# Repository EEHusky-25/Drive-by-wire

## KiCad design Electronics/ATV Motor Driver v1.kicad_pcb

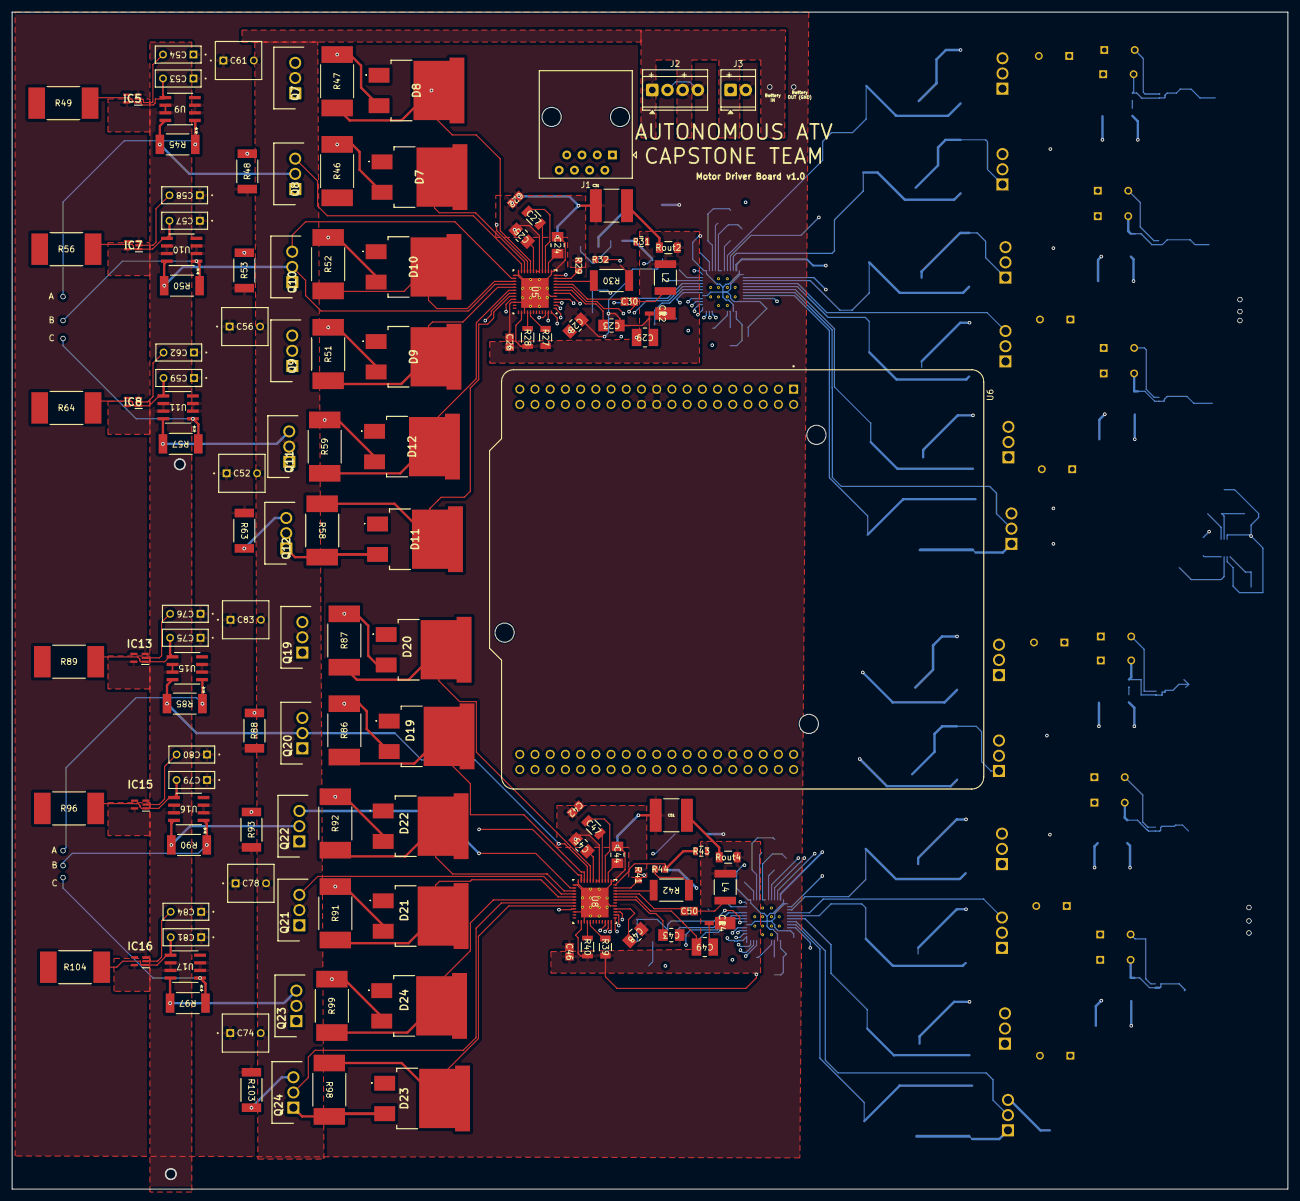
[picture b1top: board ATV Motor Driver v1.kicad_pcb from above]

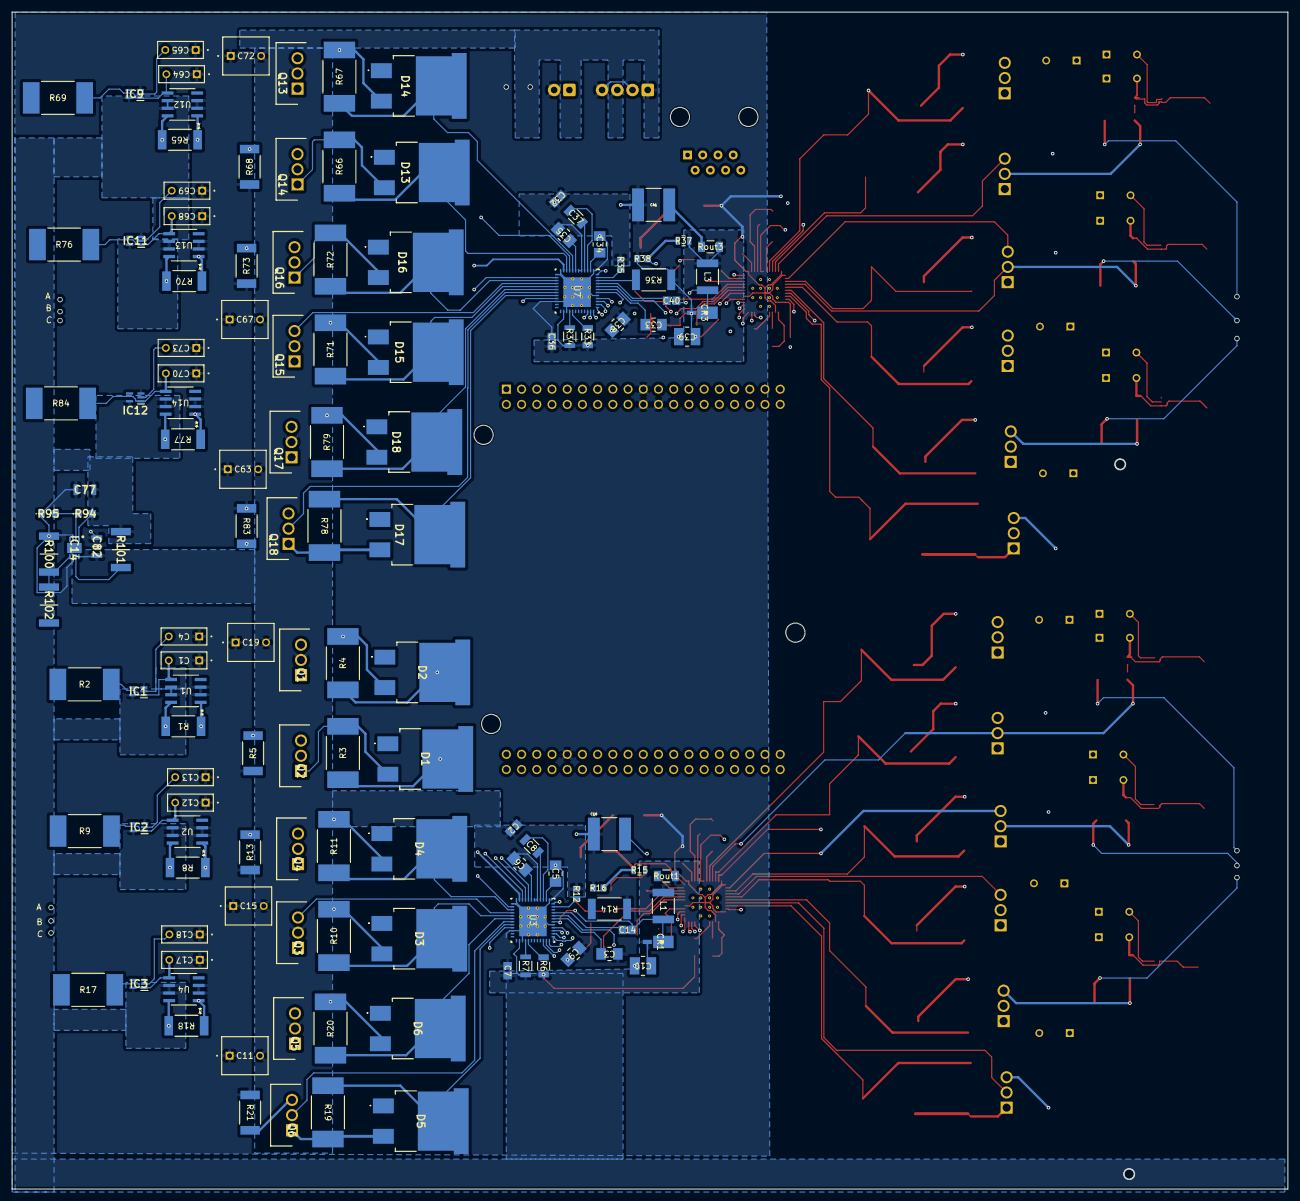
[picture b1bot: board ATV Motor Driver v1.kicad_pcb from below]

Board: 4 copper layers, 213.0 x 196.5 mm, 260 parts (132 on the bottom side), 210 nets.

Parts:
C1, C12, C17, C53, C57, C59, C64, C68, C70, C75, C79, C81: R82EC1100AA50J; CAP_R82E-7P4X2P6-5P0_KEM
C2, C7, C22, C26, C32, C36, C42, C46: C0805C104K1RECAUTO; CAPC220145_110N_KEM
C3, C5, C6, C9, C23, C24, C25, C28, C33, C34, C35, C38, C43, C44, C45, C48: C1206X105K1RACAUTO; CAPC370195_180N_KEM
C4, C13, C18, C54, C58, C62, C65, C69, C73, C76, C80, C84: R82EC2150AA50K; CAP_R82E-7P4X2P6-5P0_KEM
C8, C27, C37, C47: C1206C474K1RECAUTO; CAPC340180_180N_KEM
C10, C29, C39, C49: C1210X474K1RACAUTO; CAPC370290_115N_KEM
C11, C15, C19, C52, C56, C61, C63, C67, C72, C74, C78, C83: R82EC4100DQ70J; CAP_R82E-7P5X6P1-5P0_KEM
C14, C30, C40, C50: C0805C103K1RACAUTO; CAPC220145_88N_KEM
C16, C31, C41, C51: KRM55WR72A226MH01L; CAPC6153X670N
C77, C82: CGA5L2X7R1E105K160AA; CAPC3216X190N
CR1, CR2, CR3, CR4: UPS115UE3/TR7; POWERMITE1_DO-216AA_MIS_MCH
D1, D2, D3, D4, D5, D6, D7, D8, D9, D10, D11, D12, D13, D14, D15, D16, D17, D18, D19, D20, D21, D22, D23, D24: YQ20NL10SDTL; YQ30NL10SEFHTL
IC1, IC2, IC3, IC5, IC7, IC8, IC9, IC11, IC12, IC13, IC15, IC16: SN74LVC1G66DCKR; SOT65P210X110-5N
IC14: ADPL42005ACPZ-5.0-R7; SON50P300X300X85-9N-D
J1: RJ45; RJ45_Amphenol_54602-x08_Horizontal
J2: Screw_Terminal_01x04; TerminalBlock_TE_282834-4_1x04_P2.54mm_Horizontal
J3: Screw_Terminal_01x02; TerminalBlock_TE_282834-2_1x02_P2.54mm_Horizontal
L1, L2, L3, L4: B82432T1274K000; IND_EPCOS_B82432T_EPC
Q1, Q2, Q3, Q4, Q5, Q6, Q7, Q8, Q9, Q10, Q11, Q12, Q13, Q14, Q15, Q16, Q17, Q18, Q19, Q20, Q21, Q22, Q23, Q24: R6020ENXC7G; TO254P500X1010X2050-3P
R1, R5, R8, R13, R18, R21, R45, R48, R50, R53, R57, R63, R65, R68, R70, R73, R77, R83, R85, R88, R90, R93, R97, R103: VMS-R500-1.0-U; RES_VMS-R500-1.0-U_IAT
R2, R3, R4, R9, R10, R11, R17, R19, R20, R46, R47, R49, R51, R52, R56, R58, R59, R64, R66, R67, R69, R71, R72, R76, R78, R79, R84, R86, R87, R89, R91, R92, R96, R98, R99, R104: 35501K0JT; RES_3550_TEC
R6, R27, R33, R39: RMCF1206JT1K00; STA_RMCF1206_STP
R7, R28, R34, R40: RNCF1206TKY10K0; STA_RNCF1206_STP
R12, R29, R35, R41: ERJ-6ENF3243V; RC0805N_PAN
R14, R30, R36, R42: RMCF2512FT332K; RES_RMCF2512_STP
R15, R31, R37, R43: CRCW08053K01FKEA; RES_CRCW_0805
R16, R32, R38, R44: ERA-6AEB102V; RC0805N_PAN
R94: ERJ-UP6D6202V; ERJUP6
R95: ERJ-UP6D2002V; ERJUP6
R100, R101, R102: RCV2512100KFKEGAT; RESC6332X70N
Rout1, Rout2, Rout3, Rout4: RMCF1206FT3R00; RES_RMCF1206_STP
U1, U2, U4, U9, U10, U11, U12, U13, U14, U15, U16, U17: AD8418WBRZ; R_8_ADI
U3, U5, U7, U8: DRV8353RHRGZR; RGZ0048L
U6: NUCLEO-L476RG; MODULE_NUCLEO-L476RG

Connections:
/3-Phase H-Bridge1/CURRENT_FILTER: IC5.4 (C), IC7.4 (C), IC8.4 (C)
/3-Phase H-Bridge1/GH_A1: D8.2 (K_1), R47.1, U5.8 (GHA)
/3-Phase H-Bridge1/GH_B1: D9.2 (K_1), R51.1, U5.17 (GHB)
/3-Phase H-Bridge1/GH_C1: D12.2 (K_1), R59.1, U5.18 (GHC)
/3-Phase H-Bridge1/GL_A1: D7.2 (K_1), R46.1, U5.10 (GLA)
/3-Phase H-Bridge1/GL_B1: D10.2 (K_1), R52.1, U5.15 (GLB)
/3-Phase H-Bridge1/GL_C1: D11.2 (K_1), R58.1, U5.20 (GLC)
/3-Phase H-Bridge1/PH_A: R45.1, U9.1 (-IN)
/3-Phase H-Bridge1/PH_B: R50.1, U10.1 (-IN)
/3-Phase H-Bridge1/PH_C: R57.1, U11.1 (-IN)
/3-Phase H-Bridge1/SH_A1: Q7.3 (S), Q8.2 (D), R45.2, U5.9 (SHA), U9.8 (+IN)
/3-Phase H-Bridge1/SH_B1: Q9.3 (S), Q10.2 (D), R50.2, U5.16 (SHB), U10.8 (+IN)
/3-Phase H-Bridge1/SH_C1: Q11.3 (S), Q12.2 (D), R57.2, U5.19 (SHC), U11.8 (+IN)
/3-Phase H-Bridge1/SPA1: Q8.3 (S), R48.2, U5.11 (SPA)
/3-Phase H-Bridge1/SPB1: Q10.3 (S), R53.2, U5.14 (SPB)
/3-Phase H-Bridge1/SPC1: Q12.3 (S), R63.2, U5.21 (SPC)
/3-Phase H-Bridge1/SW1: C53.2, IC5.1 (A), R49.2, U9.5 (OUT)
/3-Phase H-Bridge1/SW2: C57.2, IC7.1 (A), R56.2, U10.5 (OUT)
/3-Phase H-Bridge1/SW3: C59.2, IC8.1 (A), R64.2, U11.5 (OUT)
/3-Phase H-Bridge2/CURRENT_FILTER: IC9.4 (C), IC11.4 (C), IC12.4 (C)
/3-Phase H-Bridge2/GH_A1: D14.2 (K_1), R67.1, U7.8 (GHA)
/3-Phase H-Bridge2/GH_B1: D15.2 (K_1), R71.1, U7.17 (GHB)
/3-Phase H-Bridge2/GH_C1: D18.2 (K_1), R79.1, U7.18 (GHC)
/3-Phase H-Bridge2/GL_A1: D13.2 (K_1), R66.1, U7.10 (GLA)
/3-Phase H-Bridge2/GL_B1: D16.2 (K_1), R72.1, U7.15 (GLB)
/3-Phase H-Bridge2/GL_C1: D17.2 (K_1), R78.1, U7.20 (GLC)
/3-Phase H-Bridge2/PH_A: R65.1, U12.1 (-IN)
/3-Phase H-Bridge2/PH_B: R70.1, U13.1 (-IN)
/3-Phase H-Bridge2/PH_C: R77.1, U14.1 (-IN)
/3-Phase H-Bridge2/SH_A1: Q13.3 (S), Q14.2 (D), R65.2, U7.9 (SHA), U12.8 (+IN)
/3-Phase H-Bridge2/SH_B1: Q15.3 (S), Q16.2 (D), R70.2, U7.16 (SHB), U13.8 (+IN)
/3-Phase H-Bridge2/SH_C1: Q17.3 (S), Q18.2 (D), R77.2, U7.19 (SHC), U14.8 (+IN)
/3-Phase H-Bridge2/SPA1: Q14.3 (S), R68.2, U7.11 (SPA)
/3-Phase H-Bridge2/SPB1: Q16.3 (S), R73.2, U7.14 (SPB)
/3-Phase H-Bridge2/SPC1: Q18.3 (S), R83.2, U7.21 (SPC)
/3-Phase H-Bridge2/SW1: C64.2, IC9.1 (A), R69.2, U12.5 (OUT)
/3-Phase H-Bridge2/SW2: C68.2, IC11.1 (A), R76.2, U13.5 (OUT)
/3-Phase H-Bridge2/SW3: C70.2, IC12.1 (A), R84.2, U14.5 (OUT)
/3-Phase H-Bridge3/CURRENT_FILTER: IC13.4 (C), IC15.4 (C), IC16.4 (C)
/3-Phase H-Bridge3/GH_A1: D20.2 (K_1), R87.1, U8.8 (GHA)
/3-Phase H-Bridge3/GH_B1: D21.2 (K_1), R91.1, U8.17 (GHB)
/3-Phase H-Bridge3/GH_C1: D24.2 (K_1), R99.1, U8.18 (GHC)
/3-Phase H-Bridge3/GL_A1: D19.2 (K_1), R86.1, U8.10 (GLA)
/3-Phase H-Bridge3/GL_B1: D22.2 (K_1), R92.1, U8.15 (GLB)
/3-Phase H-Bridge3/GL_C1: D23.2 (K_1), R98.1, U8.20 (GLC)
/3-Phase H-Bridge3/PH_A: R85.1, U15.1 (-IN)
/3-Phase H-Bridge3/PH_B: R90.1, U16.1 (-IN)
/3-Phase H-Bridge3/PH_C: R97.1, U17.1 (-IN)
/3-Phase H-Bridge3/SH_A1: Q19.3 (S), Q20.2 (D), R85.2, U8.9 (SHA), U15.8 (+IN)
/3-Phase H-Bridge3/SH_B1: Q21.3 (S), Q22.2 (D), R90.2, U8.16 (SHB), U16.8 (+IN)
/3-Phase H-Bridge3/SH_C1: Q23.3 (S), Q24.2 (D), R97.2, U8.19 (SHC), U17.8 (+IN)
/3-Phase H-Bridge3/SPA1: Q20.3 (S), R88.2, U8.11 (SPA)
/3-Phase H-Bridge3/SPB1: Q22.3 (S), R93.2, U8.14 (SPB)
/3-Phase H-Bridge3/SPC1: Q24.3 (S), R103.2, U8.21 (SPC)
/3-Phase H-Bridge3/SW1: C75.2, IC13.1 (A), R89.2, U15.5 (OUT)
/3-Phase H-Bridge3/SW2: C79.2, IC15.1 (A), R96.2, U16.5 (OUT)
/3-Phase H-Bridge3/SW3: C81.2, IC16.1 (A), R104.2, U17.5 (OUT)
/3-Phase H-Bridge/CURRENT_FILTER: IC1.4 (C), IC2.4 (C), IC3.4 (C)
/3-Phase H-Bridge/GH_A1: D2.2 (K_1), R4.1, U3.8 (GHA)
/3-Phase H-Bridge/GH_B1: D3.2 (K_1), R10.1, U3.17 (GHB)
/3-Phase H-Bridge/GH_C1: D6.2 (K_1), R20.1, U3.18 (GHC)
/3-Phase H-Bridge/GL_A1: D1.2 (K_1), R3.1, U3.10 (GLA)
/3-Phase H-Bridge/GL_B1: D4.2 (K_1), R11.1, U3.15 (GLB)
/3-Phase H-Bridge/GL_C1: D5.2 (K_1), R19.1, U3.20 (GLC)
/3-Phase H-Bridge/PH_A: R1.1, U1.1 (-IN)
/3-Phase H-Bridge/PH_B: R8.1, U2.1 (-IN)
/3-Phase H-Bridge/PH_C: R18.1, U4.1 (-IN)
/3-Phase H-Bridge/SH_A1: Q1.3 (S), Q2.2 (D), R1.2, U1.8 (+IN), U3.9 (SHA)
/3-Phase H-Bridge/SH_B1: Q3.3 (S), Q4.2 (D), R8.2, U2.8 (+IN), U3.16 (SHB)
/3-Phase H-Bridge/SH_C1: Q5.3 (S), Q6.2 (D), R18.2, U3.19 (SHC), U4.8 (+IN)
/3-Phase H-Bridge/SPA1: Q2.3 (S), R5.2, U3.11 (SPA)
/3-Phase H-Bridge/SPB1: Q4.3 (S), R13.2, U3.14 (SPB)
/3-Phase H-Bridge/SPC1: Q6.3 (S), R21.2, U3.21 (SPC)
/3-Phase H-Bridge/SW1: C1.2, IC1.1 (A), R2.2, U1.5 (OUT)
/3-Phase H-Bridge/SW2: C12.2, IC2.1 (A), R9.2, U2.5 (OUT)
/3-Phase H-Bridge/SW3: C17.2, IC3.1 (A), R17.2, U4.5 (OUT)
/3-Phase H-Bridge/Supply: C2.2, C6.2, C11.2, C15.2, C19.2, C22.2, C25.2, C32.2, C35.2, C42.2, C45.2, C52.2, C56.2, C61.2, C63.2, C67.2, C72.2, C74.2, C78.2, C82.2, C83.2, IC14.8 (VIN), J2.1, J2.3, Q1.2 (D), Q3.2 (D), Q5.2 (D), Q7.2 (D), Q9.2 (D), Q11.2 (D), Q13.2 (D), Q15.2 (D), Q17.2 (D), Q19.2 (D), Q21.2 (D), Q23.2 (D), R12.1, R29.1, R35.1, R41.1, U3.5 (VM), U3.6 (VDRAIN), U5.5 (VM), U5.6 (VDRAIN), U7.5 (VM), U7.6 (VDRAIN), U8.5 (VM), U8.6 (VDRAIN)
/Gate Driver1/FAULT1: R28.1, U5.28 (FAULT_N)
/Gate Driver1/INHA1: U5.34 (INHA), U6.CN7_29 (PH0)
/Gate Driver1/INHB1: U5.36 (INHB), U6.CN7_27 (PC15)
/Gate Driver1/INHC1: U5.38 (INHC), U6.CN7_23 (PC13)
/Gate Driver1/INLA1: U5.35 (INLA), U6.CN7_28 (PA0)
/Gate Driver1/INLB1: U5.37 (INLB), U6.CN7_25 (PC14)
/Gate Driver1/INLC1: U5.39 (INLC), U6.CN7_21 (PB7)
/Gate Driver1/SDO1: R27.1, U5.29 (MODE_SDO)
/Gate Driver2/FAULT1: R34.1, U7.28 (FAULT_N)
/Gate Driver2/INHA1: U6.CN7_1 (PC10), U7.34 (INHA)
/Gate Driver2/INHB1: U6.CN7_3 (PC12), U7.36 (INHB)
/Gate Driver2/INHC1: U6.CN7_5 (VDD), U7.38 (INHC)
/Gate Driver2/INLA1: U6.CN7_2 (PC11), U7.35 (INLA)
/Gate Driver2/INLB1: U6.CN7_4 (PD2), U7.37 (INLB)
/Gate Driver2/INLC1: U6.CN7_6 (E5V), U7.39 (INLC)
/Gate Driver2/SDO1: R33.1, U7.29 (MODE_SDO)
/Gate Driver3/FAULT1: R40.1, U8.28 (FAULT_N)
/Gate Driver3/INHA1: U6.CN10_37 (PA3), U8.34 (INHA)
/Gate Driver3/INHB1: U6.CN10_33 (PA10), U8.36 (INHB)
/Gate Driver3/INHC1: U6.CN10_31 (PB3), U8.38 (INHC)
/Gate Driver3/INLA1: U6.CN10_35 (PA2), U8.35 (INLA)
/Gate Driver3/INLB1: U6.CN10_34 (PC4), U8.37 (INLB)
/Gate Driver3/INLC1: U6.CN10_30 (PB13), U8.39 (INLC)
/Gate Driver3/SDO1: R39.1, U8.29 (MODE_SDO)
/Gate Driver/FAULT1: R7.1, U3.28 (FAULT_N)
/Gate Driver/INHA1: U3.34 (INHA), U6.CN10_16 (PB12)
/Gate Driver/INHB1: U3.36 (INHB), U6.CN10_13 (PA6)
/Gate Driver/INHC1: U3.38 (INHC), U6.CN10_12 (PA12)
/Gate Driver/INLA1: U3.35 (INLA), U6.CN10_15 (PA7)
/Gate Driver/INLB1: U3.37 (INLB), U6.CN10_14 (PA11)
/Gate Driver/INLC1: U3.39 (INLC), U6.CN10_11 (PA5)
/Gate Driver/SDO1: R6.1, U3.29 (MODE_SDO)
GND: C1.1, C2.1, C3.1, C4.1, C5.1, C7.1, C9.1, C10.1, C11.1, C12.1, C13.1, C15.1, C16.1, C17.1, C18.1, C19.1, C22.1, C23.1, C24.1, C26.1, C28.1, C29.1, C31.1, C32.1, C33.1, C34.1, C36.1, C38.1, C39.1, C41.1, C42.1, C43.1, C44.1, C46.1, C48.1, C49.1, C51.1, C52.1, C53.1, C54.1, C56.1, C57.1, C58.1, C59.1, C61.1, C62.1, C63.1, C64.1, C65.1, C67.1, C68.1, C69.1, C70.1, C72.1, C73.1, C74.1, C75.1, C76.1, C77.1, C78.1, C79.1, C80.1, C81.1, C82.1, C83.1, C84.1, CR1.2, CR2.2, CR3.2, CR4.2, IC1.3 (GND), IC2.3 (GND), IC3.3 (GND), IC5.3 (GND), IC7.3 (GND), IC8.3 (GND), IC9.3 (GND), IC11.3 (GND), IC12.3 (GND), IC13.3 (GND), IC14.3 (GND_1), IC14.6 (GND_2), IC15.3 (GND), IC16.3 (GND), J2.2, J2.4, J3.2, R5.1, R13.1, R14.1, R16.1, R21.1, R30.1, R32.1, R36.1, R38.1, R42.1, R44.1, R48.1, R53.1, R63.1, R68.1, R73.1, R83.1, R88.1, R93.1, R95.1, R100.1, R103.1, U1.2 (GND), U1.3 (VREF2), U2.2 (GND), U2.3 (VREF2), U3.1 (PGND), U3.12 (SNA), U3.13 (SNB), U3.22 (SNC), U3.27 (AGND), U3.41 (DGND), U3.49 (PAD), U4.2 (GND), U4.3 (VREF2), U5.1 (PGND), U5.12 (SNA), U5.13 (SNB), U5.22 (SNC), U5.27 (AGND), U5.41 (DGND), U5.49 (PAD), U6.CN7_19 (GND_CN7_19), U6.CN7_20 (GND_CN7_20), U6.CN7_22 (GND_CN7_22), U6.CN10_9 (GND_CN10_9), U7.1 (PGND), U7.12 (SNA), U7.13 (SNB), U7.22 (SNC), U7.27 (AGND), U7.41 (DGND), U7.49 (PAD), U8.1 (PGND), U8.12 (SNA), U8.13 (SNB), U8.22 (SNC), U8.27 (AGND), U8.41 (DGND), U8.49 (PAD), U9.2 (GND), U9.3 (VREF2), U10.2 (GND), U10.3 (VREF2), U11.2 (GND), U11.3 (VREF2), U12.2 (GND), U12.3 (VREF2), U13.2 (GND), U13.3 (VREF2), U14.2 (GND), U14.3 (VREF2), U15.2 (GND), U15.3 (VREF2), U16.2 (GND), U16.3 (VREF2), U17.2 (GND), U17.3 (VREF2)
unnamed: C16.2, Rout1.1
unnamed: C31.2, Rout2.1
unnamed: C41.2, Rout3.1
unnamed: C51.2, Rout4.1
unnamed: D1.3 (A), Q2.1 (G), R3.2
unnamed: D2.3 (A), Q1.1 (G), R4.2
unnamed: D3.3 (A), Q3.1 (G), R10.2
unnamed: D4.3 (A), Q4.1 (G), R11.2
unnamed: D5.3 (A), Q6.1 (G), R19.2
unnamed: D6.3 (A), Q5.1 (G), R20.2
unnamed: D7.3 (A), Q8.1 (G), R46.2
unnamed: D8.3 (A), Q7.1 (G), R47.2
unnamed: D9.3 (A), Q9.1 (G), R51.2
unnamed: D10.3 (A), Q10.1 (G), R52.2
unnamed: D11.3 (A), Q12.1 (G), R58.2
unnamed: D12.3 (A), Q11.1 (G), R59.2
unnamed: D13.3 (A), Q14.1 (G), R66.2
unnamed: D14.3 (A), Q13.1 (G), R67.2
unnamed: D15.3 (A), Q15.1 (G), R71.2
unnamed: D16.3 (A), Q16.1 (G), R72.2
unnamed: D17.3 (A), Q18.1 (G), R78.2
unnamed: D18.3 (A), Q17.1 (G), R79.2
unnamed: D19.3 (A), Q20.1 (G), R86.2
unnamed: D20.3 (A), Q19.1 (G), R87.2
unnamed: D21.3 (A), Q21.1 (G), R91.2
unnamed: D22.3 (A), Q22.1 (G), R92.2
unnamed: D23.3 (A), Q24.1 (G), R98.2
unnamed: D24.3 (A), Q23.1 (G), R99.2
unnamed: C4.2, IC1.2 (B)
unnamed: C13.2, IC2.2 (B)
unnamed: C18.2, IC3.2 (B)
unnamed: C54.2, IC5.2 (B)
unnamed: C58.2, IC7.2 (B)
unnamed: C62.2, IC8.2 (B)
unnamed: C65.2, IC9.2 (B)
unnamed: C69.2, IC11.2 (B)
unnamed: C73.2, IC12.2 (B)
unnamed: C76.2, IC13.2 (B)
unnamed: IC14.5 (EN/UVLO), R100.2, R102.1
unnamed: IC14.7 (PG), R101.1
unnamed: IC14.2 (SENSE/ADJ), R94.1, R95.2
unnamed: C80.2, IC15.2 (B)
unnamed: C84.2, IC16.2 (B)
unnamed: C14.1, U3.45 (BST)
unnamed: C8.2, U3.4 (CPH)
unnamed: C8.1, U3.3 (CPL)
unnamed: C9.2, U3.40 (DVDD)
unnamed: R15.1, R16.2, U3.48 (FB)
unnamed: R14.2, U3.46 (RCL)
unnamed: R12.2, U3.47 (RT_SD)
unnamed: C14.2, CR1.1, L1.2, U3.42 (SW)
unnamed: C10.2, U3.44 (VCC)
unnamed: C6.1, U3.7 (VCP)
unnamed: C5.2, U3.2 (VGLS)
unnamed: C3.2, U3.43 (VIN)
unnamed: C30.1, U5.45 (BST)
unnamed: C27.2, U5.4 (CPH)
unnamed: C27.1, U5.3 (CPL)
unnamed: C28.2, U5.40 (DVDD)
unnamed: R31.1, R32.2, U5.48 (FB)
unnamed: R30.2, U5.46 (RCL)
unnamed: R29.2, U5.47 (RT_SD)
unnamed: C30.2, CR2.1, L2.2, U5.42 (SW)
unnamed: C29.2, U5.44 (VCC)
unnamed: C25.1, U5.7 (VCP)
unnamed: C24.2, U5.2 (VGLS)
unnamed: C23.2, U5.43 (VIN)
unnamed: J1.1, U6.CN7_30 (PA1)
unnamed: J1.3, U6.CN7_32 (PA4)
unnamed: J1.4, U6.CN7_34 (PB0)
unnamed: J1.8, U6.CN7_38 (PC0)
unnamed: J1.6, U6.CN7_36 (PC1)
unnamed: J1.5, U6.CN7_35 (PC2)
unnamed: J1.7, U6.CN7_37 (PC3)
unnamed: J1.2, U6.CN7_31 (PH1)
unnamed: C40.1, U7.45 (BST)
unnamed: C37.2, U7.4 (CPH)
unnamed: C37.1, U7.3 (CPL)
unnamed: C38.2, U7.40 (DVDD)
unnamed: R37.1, R38.2, U7.48 (FB)
unnamed: R36.2, U7.46 (RCL)
unnamed: R35.2, U7.47 (RT_SD)
unnamed: C40.2, CR3.1, L3.2, U7.42 (SW)
unnamed: C39.2, U7.44 (VCC)
unnamed: C35.1, U7.7 (VCP)
unnamed: C34.2, U7.2 (VGLS)
unnamed: C33.2, U7.43 (VIN)
unnamed: C50.1, U8.45 (BST)
unnamed: C47.2, U8.4 (CPH)
unnamed: C47.1, U8.3 (CPL)
unnamed: C48.2, U8.40 (DVDD)
unnamed: R43.1, R44.2, U8.48 (FB)
unnamed: R42.2, U8.46 (RCL)
unnamed: R41.2, U8.47 (RT_SD)
unnamed: C50.2, CR4.1, L4.2, U8.42 (SW)
unnamed: C49.2, U8.44 (VCC)
unnamed: C45.1, U8.7 (VCP)
unnamed: C44.2, U8.2 (VGLS)
unnamed: C43.2, U8.43 (VIN)
VCC: C7.2, C26.2, C36.2, C46.2, C77.2, IC1.5 (VCC), IC2.5 (VCC), IC3.5 (VCC), IC5.5 (VCC), IC7.5 (VCC), IC8.5 (VCC), IC9.5 (VCC), IC11.5 (VCC), IC12.5 (VCC), IC13.5 (VCC), IC14.1 (VOUT), IC15.5 (VCC), IC16.5 (VCC), L1.1, L2.1, L3.1, L4.1, R6.2, R7.2, R15.2, R27.2, R28.2, R31.2, R33.2, R34.2, R37.2, R39.2, R40.2, R43.2, R94.2, R101.2, Rout1.2, Rout2.2, Rout3.2, Rout4.2, U1.6 (VS), U1.7 (VREF1), U2.6 (VS), U2.7 (VREF1), U3.26 (VREF), U4.6 (VS), U4.7 (VREF1), U5.26 (VREF), U6.CN7_24 (VIN), U7.26 (VREF), U8.26 (VREF), U9.6 (VS), U9.7 (VREF1), U10.6 (VS), U10.7 (VREF1), U11.6 (VS), U11.7 (VREF1), U12.6 (VS), U12.7 (VREF1), U13.6 (VS), U13.7 (VREF1), U14.6 (VS), U14.7 (VREF1), U15.6 (VS), U15.7 (VREF1), U16.6 (VS), U16.7 (VREF1), U17.6 (VS), U17.7 (VREF1)

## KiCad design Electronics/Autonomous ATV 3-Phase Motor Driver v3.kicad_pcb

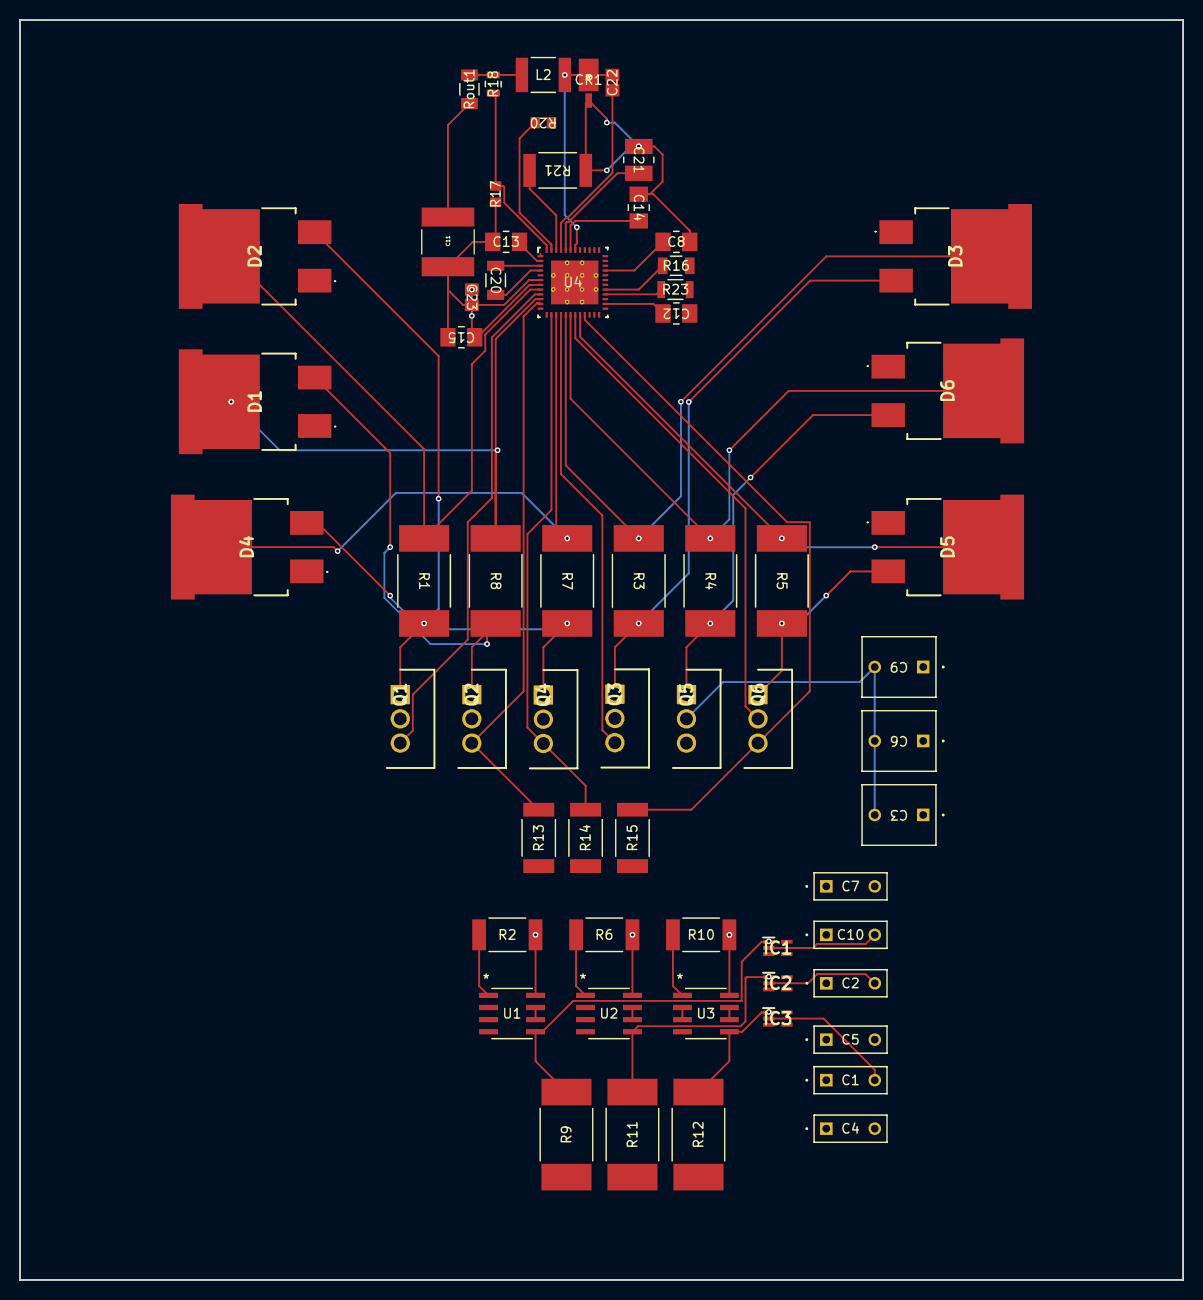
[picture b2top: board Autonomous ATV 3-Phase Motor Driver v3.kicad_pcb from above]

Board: 4 copper layers, 121.9 x 132.1 mm, 62 parts (0 on the bottom side), 50 nets.

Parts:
C1, C2, C10: R82EC2150AA50K; CAP_R82E-7P4X2P6-5P0_KEM
C3, C6, C9: R82EC4100DQ70J; CAP_R82E-7P5X6P1-5P0_KEM
C4, C5, C7: R82EC1100AA50J; CAP_R82E-7P4X2P6-5P0_KEM
C8, C12, C13, C14, C15: C1206X105K1RACAUTO; CAPC370195_180N_KEM
C11: KRM55WR72A226MH01L; CAPC6153X670N
C20: C1206C474K1RECAUTO; CAPC340180_180N_KEM
C21: C1210X474K1RACAUTO; CAPC370290_115N_KEM
C22: C0805C103K1RACAUTO; CAPC220145_88N_KEM
C23: C0805C104K1RECAUTO; CAPC220145_110N_KEM
CR1: UPS115UE3/TR7; POWERMITE1_DO-216AA_MIS_MCH
D1, D2, D3, D4, D5, D6: YQ20NL10SDTL; YQ30NL10SEFHTL
IC1, IC2, IC3: SN74LVC1G66DCKR; SOT65P210X110-5N
L2: B82432T1274K000; IND_EPCOS_B82432T_EPC
Q1, Q2, Q3, Q4, Q5, Q6: R6020ENXC7G; TO254P500X1010X2050-3P
R1, R3, R4, R5, R7, R8, R9, R11, R12: 35501K0JT; RES_3550_TEC
R2, R6, R10, R13, R14, R15: VMS-R500-1.0-U; RES_VMS-R500-1.0-U_IAT
R16: RMCF1206JT1K00; STA_RMCF1206_STP
R17: ERA-6AEB102V; RC0805N_PAN
R18: CRCW08053K01FKEA; RES_CRCW_0805
R20: ERJ-6ENF3243V; RC0805N_PAN
R21: RMCF2512FT332K; RES_RMCF2512_STP
R23: RNCF1206TKY10K0; STA_RNCF1206_STP
Rout1: RMCF1206FT3R00; RES_RMCF1206_STP
U1, U2, U3: AD8418WBRZ; R_8_ADI
U4: DRV8353RHRGZR; RGZ0048L

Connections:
/ATV Motor Driver/CURRENT_FILTER: IC1.4 (C), IC2.4 (C), IC3.4 (C)
/ATV Motor Driver/GH_A: D2.2 (K_1), R1.1, U4.8 (GHA)
/ATV Motor Driver/GH_B: D3.2 (K_1), R3.1, U4.17 (GHB)
/ATV Motor Driver/GH_C: D6.2 (K_1), R4.1, U4.18 (GHC)
/ATV Motor Driver/GL_A: D1.2 (K_1), R8.1, U4.10 (GLA)
/ATV Motor Driver/GL_B: D4.2 (K_1), R7.1, U4.15 (GLB)
/ATV Motor Driver/GL_C: D5.2 (K_1), R5.1, U4.20 (GLC)
/ATV Motor Driver/PH_A: R2.1, U1.1 (-IN)
/ATV Motor Driver/PH_B: R6.1, U2.1 (-IN)
/ATV Motor Driver/PH_C: R10.1, U3.1 (-IN)
/ATV Motor Driver/SH_A: Q1.3 (S), Q2.2 (D), R2.2, U1.8 (+IN), U4.9 (SHA)
/ATV Motor Driver/SH_B: Q3.3 (S), Q4.2 (D), R6.2, U2.8 (+IN), U4.16 (SHB)
/ATV Motor Driver/SH_C: Q5.3 (S), Q6.2 (D), R10.2, U3.8 (+IN), U4.19 (SHC)
/ATV Motor Driver/SPA: Q2.3 (S), R13.2, U4.11 (SPA)
/ATV Motor Driver/SPB: Q4.3 (S), R14.2, U4.14 (SPB)
/ATV Motor Driver/SPC: Q6.3 (S), R15.2, U4.21 (SPC)
/ATV Motor Driver/SW1: C7.2, IC1.1 (A), R9.2, U1.5 (OUT)
/ATV Motor Driver/SW2: C5.2, IC2.1 (A), R11.2, U2.5 (OUT)
/ATV Motor Driver/SW3: C4.2, IC3.1 (A), R12.2, U3.5 (OUT)
/ATV Motor Driver/Supply: C3.2, C6.2, C9.2, Q1.2 (D), Q3.2 (D), Q5.2 (D)
/DRV8350rhrgzr/FAULT: R23.1, U4.28 (FAULT_N)
/DRV8350rhrgzr/SDO: R16.1, U4.29 (MODE_SDO)
GND: C1.1, C2.1, C3.1, C4.1, C5.1, C6.1, C7.1, C8.2, C9.1, C10.1, C11.1, C12.1, C13.1, C14.1, C15.2, C21.1, C23.2, CR1.2, IC1.3 (GND), IC2.3 (GND), IC3.3 (GND), R13.1, R14.1, R15.1, R17.1, R21.1, U1.2 (GND), U1.3 (VREF2), U2.2 (GND), U2.3 (VREF2), U3.2 (GND), U3.3 (VREF2), U4.1 (PGND), U4.5 (VM), U4.6 (VDRAIN), U4.12 (SNA), U4.13 (SNB), U4.22 (SNC), U4.27 (AGND), U4.40 (DVDD), U4.41 (DGND), U4.49 (PAD)
unnamed: C11.2, Rout1.1
unnamed: D1.3 (A), Q2.1 (G), R8.2
unnamed: D2.3 (A), Q1.1 (G), R1.2
unnamed: D3.3 (A), Q3.1 (G), R3.2
unnamed: D4.3 (A), Q4.1 (G), R7.2
unnamed: D5.3 (A), Q6.1 (G), R5.2
unnamed: D6.3 (A), Q5.1 (G), R4.2
unnamed: C10.2, IC1.2 (B)
unnamed: C2.2, IC2.2 (B)
unnamed: C1.2, IC3.2 (B)
unnamed: L2.1, R18.2, Rout1.2
unnamed: U1.6 (VS), U1.7 (VREF1)
unnamed: U2.6 (VS), U2.7 (VREF1)
unnamed: U3.6 (VS), U3.7 (VREF1)
unnamed: C22.1, U4.45 (BST)
unnamed: C20.2, U4.4 (CPH)
unnamed: C20.1, U4.3 (CPL)
unnamed: C8.1, U4.33 (ENABLE)
unnamed: R17.2, R18.1, U4.48 (FB)
unnamed: R21.2, U4.46 (RCL)
unnamed: R20.2, U4.47 (RT_SD)
unnamed: C22.2, CR1.1, L2.2, U4.42 (SW)
unnamed: C21.2, U4.44 (VCC)
unnamed: C15.1, C23.1, U4.7 (VCP)
unnamed: C13.2, U4.2 (VGLS)
unnamed: C14.2, U4.43 (VIN)
unnamed: C12.2, U4.26 (VREF)

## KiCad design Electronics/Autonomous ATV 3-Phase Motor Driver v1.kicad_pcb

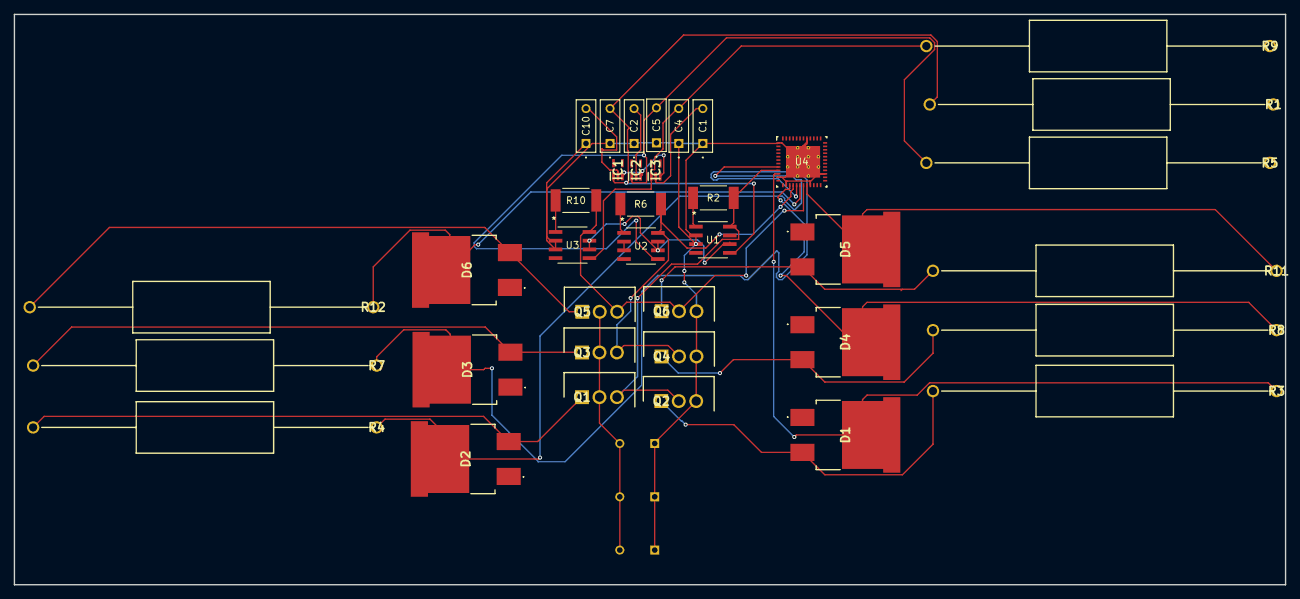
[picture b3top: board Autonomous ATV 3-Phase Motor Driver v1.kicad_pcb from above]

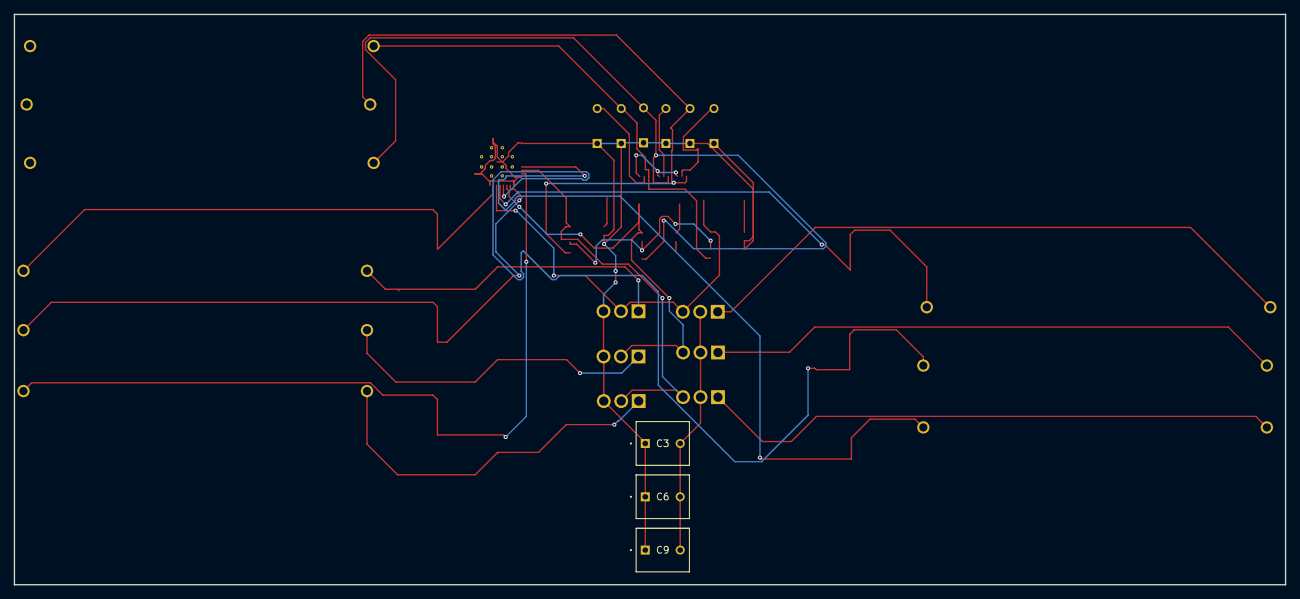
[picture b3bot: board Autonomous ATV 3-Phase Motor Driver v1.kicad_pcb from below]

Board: 2 copper layers, 185.0 x 83.0 mm, 40 parts (3 on the bottom side), 28 nets.

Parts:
C1, C2, C10: R82EC2150AA50K; CAP_R82E-7P4X2P6-5P0_KEM
C3, C6, C9: R82EC4100DQ70J; CAP_R82E-7P5X6P1-5P0_KEM
C4, C5, C7: R82EC1100AA50J; CAP_R82E-7P4X2P6-5P0_KEM
D1, D2, D3, D4, D5, D6: YQ20NL10SDTL; YQ30NL10SEFHTL
IC1, IC2, IC3: SN74LVC1G66DCKR; SOT65P210X110-5N
Q1, Q2, Q3, Q4, Q5, Q6: R6020ENXC7G; TO254P500X1010X2050-3P
R1, R3, R4, R5, R7, R8, R9, R11, R12: WHE1K0FET; RESAD5000W100L2000D750
R2, R6, R10: VMS-R500-1.0-U; RES_VMS-R500-1.0-U_IAT
U1, U2, U3: AD8418WBRZ; R_8_ADI
U4: DRV8350RHRGZR; RGZ0048L

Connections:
/ATV Motor Driver/CURRENT_FILTER: IC1.4 (C), IC2.4 (C), IC3.4 (C)
/ATV Motor Driver/GH_A: D2.2 (K_1), R4.1, U4.8 (GHA)
/ATV Motor Driver/GH_B: D3.2 (K_1), R7.1, U4.17 (GHB)
/ATV Motor Driver/GH_C: D6.2 (K_1), R12.1, U4.18 (GHC)
/ATV Motor Driver/GL_A: D1.2 (K_1), R3.1, U4.10 (GLA)
/ATV Motor Driver/GL_B: D4.2 (K_1), R8.1, U4.15 (GLB)
/ATV Motor Driver/GL_C: D5.2 (K_1), R11.1, U4.20 (GLC)
/ATV Motor Driver/PH_A: R2.1, U1.1 (-IN)
/ATV Motor Driver/PH_B: R6.1, U2.1 (-IN)
/ATV Motor Driver/PH_C: R10.1, U3.1 (-IN)
/ATV Motor Driver/SH_A: Q1.3 (S), Q2.2 (D), R2.2, U1.8 (+IN), U4.9 (SHA)
/ATV Motor Driver/SH_B: Q3.3 (S), Q4.2 (D), R6.2, U2.8 (+IN), U4.16 (SHB)
/ATV Motor Driver/SH_C: Q5.3 (S), Q6.2 (D), R10.2, U3.8 (+IN), U4.19 (SHC)
/ATV Motor Driver/SW1: C7.2, IC1.1 (A), R1.2, U1.5 (OUT)
/ATV Motor Driver/SW2: C5.2, IC2.1 (A), R5.2, U2.5 (OUT)
/ATV Motor Driver/SW3: C4.2, IC3.1 (A), R9.2, U3.5 (OUT)
/ATV Motor Driver/Supply: C3.2, C6.2, C9.2, Q1.2 (D), Q3.2 (D), Q5.2 (D)
/ATV Motor Driver/VCC: IC1.5 (VCC), IC2.5 (VCC), IC3.5 (VCC), U1.6 (VS), U1.7 (VREF1), U2.6 (VS), U2.7 (VREF1), U3.6 (VS), U3.7 (VREF1)
GND: C1.1, C2.1, C3.1, C4.1, C5.1, C6.1, C7.1, C9.1, C10.1, IC1.3 (GND), IC2.3 (GND), IC3.3 (GND), Q2.3 (S), Q4.3 (S), Q6.3 (S), U1.2 (GND), U1.3 (VREF2), U2.2 (GND), U2.3 (VREF2), U3.2 (GND), U3.3 (VREF2), U4.1 (PGND), U4.11 (SLA), U4.14 (SLB), U4.21 (SLC), U4.27 (AGND), U4.41 (DGND), U4.49 (PAD)
unnamed: D1.3 (A), Q2.1 (G), R3.2
unnamed: D2.3 (A), Q1.1 (G), R4.2
unnamed: D3.3 (A), Q3.1 (G), R7.2
unnamed: D4.3 (A), Q4.1 (G), R8.2
unnamed: D5.3 (A), Q6.1 (G), R11.2
unnamed: D6.3 (A), Q5.1 (G), R12.2
unnamed: C10.2, IC1.2 (B)
unnamed: C2.2, IC2.2 (B)
unnamed: C1.2, IC3.2 (B)

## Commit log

2025-08-19 Create Arduino DBW Receiver code
    Arduino code for the receival of CAN messages, not fully developed but required for receiving messages while running Jetson Nano Autonomous code.
2025-08-21 Create Autonomous_DUE_Code
    Unfinished & Unpolished C++ Code for Arduino DUE for functioning autonomously in conjunction with the JetHawk code for autonomous waypoint navigation, found in JetHawk repository.
